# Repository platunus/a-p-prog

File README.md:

# Programmer for 8-bit PIC devices built upon AVR (or Arduino) or WCH CH55x

For [Micro progmeter](https://github.com/jaromir-sukuba/micro_progmeter) project I want to deliver full set of open-source materials, but it would be shame if folks trying to replicate the project would have to buy another programmer to flash the PIC MCU, so I decided to do a little bit of brain stretching and implement PIC16F1xxx programmer with... Arduino. I really can't say I love this platform, but it is low cost and available.
Together with SDCC compiler this serves as completely open-source basis for many 8-bit PIC devices.

The current project status: Programmer working, sources need cleanup, perhaps rework of its structure (it grew out of its simple structure).
# List of supported devices is at the end of this page.

## Hardware
There are two options fo hardware for this project:

### Hardware option 1 - Arduino hardware
Take any Arduino with ATmega328P or ATmega32u4, like Uno, pro micro or most of cheap chinese knock-off boards. Considering the target has its own power supply, connect GND, MCLR, PGC and PGD lines to respective pins on arduino as follows:

| Arduino pin | AVR pin | Target PIC pin | Comment                                                                     |
|-------------|---------|----------------|-----------------------------------------------------------------------------|
| GND         | GND     | GND            | common ground                                                               |
| 5V          | VDD     | VDD            | optional*- power supply for PIC MCU, you may power target from other source |
| A3          | PC3     | MCLR           | reset line of PIC MCU                                                       |
| A1          | PC1     | PGD            | programming data line                                                       |
| A0          | PC0     | PGC            | programming clock line                                                      |

* If you are powering target PIC from other power source (in circuit programming), series resistors (something like 470-1000 Ohms) in MCLR, PGC and PGD lines are good idea, it will somehow decrease currents flowing through IO pins due to power supplies differences between arduino and target board. In this configuration, even targets running at 3,3V are possible to program, though it is dirty practice.

Power it up, no smoke should be released. Run arduino IDE, open programmer firmware from here (/fw/pp.ino), complie and upload to arduino board - now you have PIC programmer ready to go. Go to software below.

The programmer is proven to work with some generic Uno board from china, as well as chinese arduino-nano clone

The [Pro Micro ICSP shield](https://github.com/hanyazou/Pro-Micro-ICSP-shield) is a tiny "shield" for Arduino Pro Micro which featured ATmega32u4.
This tiny board simply connect ATMEGA 32u4's A0, A1 and A3 to PIC's MCLR, PGD and PGC, but acts as a PIC programmer.

### Hardware option 2 - dedicated board
I designed this little board, see at /hw directory

Considering the target has its own power supply, connect GND, MCLR, PGC and PGD lines to respective pins on PIC programmer (notice the pinout similar to PICkit programmers). Vdd line is not currently used ad it is not needed for operation of programmer, but future revisions of firmware may take advantage of this pin and detect target VDD.
The hardware works with both FT232RL and CY7C65213 in place of USB/serial converter. Both were proven to work, with no other hardware difference.

Use [another arduino](https://www.arduino.cc/en/Tutorial/ArduinoISP) (or proper ISP programmer) to load Arduino UNO bootloader to PIC programmer board (performed only once), turning it into regular arduino compatible board.

Ensure JP2 is closed, then you can load new firmware into PIC programmer using regular Arduino IDE. Open jumper JP2. Now you have your programmer ready to go, move on to software.
The firmware should be able to compile outside Arduino IDE as it doesn't contain any Arduino-specific stuff, though I haven't tried that.

### Hardware option 3 - WCH CH552/CH554
Take WCH CH552/CH554 with USB device PHY. Considering the target has its own power supply, connect GND, MCLR, PGC and PGD lines to respective pins on CH55x as follows:

| CH55x pin | Target PIC pin | Comment                                                                     |
|-----------|----------------|-----------------------------------------------------------------------------|
| GND       | GND            | common ground                                                               |
| VDD (5V)  | VDD            | optional*- power supply for PIC MCU, you may power target from other source |
| P1.4      | N/C            | optional- indicator: connected LED with 1k ohm resistor                     |
| P1.5      | MCLR           | reset line of PIC MCU                                                       |
| P1.6      | PGD            | programming data line                                                       |
| P1.7      | PGC            | programming clock line                                                      |

* If you are powering target PIC from other power source (in circuit programming), series resistors (something like 470-1000 Ohms) in MCLR, PGC and PGD lines are good idea, it will somehow decrease currents flowing through IO pins due to power supplies differences between arduino and target board. In this configuration, even targets running at 3,3V are possible to program, though it is dirty practice.

Run arduino IDE, install [CH55xDuino](https://github.com/DeqingSun/ch55xduino), open programmer firmware from here (/fw/pp.ino), select CH552 board, complie and upload to CH55x - now you have PIC programmer ready to go. Go to software below.

## Software

When running under Linux, download source from this repository and run

`gcc -Wall pp3.c -o pp3`

This should build executable pp3. When working under windows, you can download compiled binary from this repository. Alternatively, you can build it from source - install minGW and run

`gcc -Wall pp3.c -o pp3`

ie. the same procedure as on Linux. This should result in silent build with pp3.exe executable created.

Running the executable with no parameters should only bring banner "pp programmer". Though running with basic set of parameters

`./pp3 -c /dev/ttyACM0 -t 16f1829 file.hex`

under Linux, where -c parameter denotes port to be accessed, -t parameter defines PIC to be programmed and last parameter is hex file to be downloaded; or

`pp3.exe -c COM30 -t 16f1829 file.hex`

under Windows should program the target PIC; with expected result:

	$ ./pp3 -c /dev/ttyACM0 -t 16f1829 file.hex
    Opening serial port
    Device ID 0x27E4
    Programming FLASH (16384 B in 256 pages)
    Programming config
    Verifying FLASH (16384 B in 256 pages)
    Verifying config
    Releasing MCLR

## Notes on software

If you are running the hardware on generic arduino board or you forget to open jumper JP2 after loading firmware on dedicated hardware, you may need to insert waiting time after opening serial port and before communication - to ensure Arduino bootloader times out after opening serial port and takes control to programmer firmware. It should look like this

`pp3.exe -c COM30 -s 1700 -t 16f1829 file.bin`

where number after -s switch defines the number of miliseconds to wait after opening the serial port.

You may omit the actual programming using -p switch or verification using -n switch, when using both the programmer only checks target device signature and exits.

`$ ./pp3 -c /dev/ttyACM0 -p -n -t 16f1829 file.bin`

    Opening serial port
    Device ID 0x27E4
    Releasing MCLR

you can add some debug output info using -v parameter, ranging from -v 1 to -v 4. It may be suitable for debugging, -v 4 prints out all byte transaction on serial port, so be prepared for huge output.
There is database file pp3_devices.dat which hold information of supported PIC types. For now, the filename is fixed in code can't be changed and file has to be in the same directory as pp executable..

## Supported devices

Obviously, there is more supported than verified (tested) devices. I tried to test at least one device from specific family. The members from one family are usually very very similar, giving me enough confidence to mark them as supproted. Of course, typos can happen, but those are easy to correct.

**DEVICE**|**TESTED**
:-----:|:-----:
PIC12F1501|YES
PIC12F1571| 
PIC12F1572|YES
PIC12F1612|YES
PIC12F1822|YES
PIC12F1840|YES
PIC12LF1501|YES
PIC12LF1552|YES
PIC12LF1571| 
PIC12LF1572| 
PIC12LF1612| 
PIC12LF1822| 
PIC12LF1840|YES
PIC16F1454| 
PIC16F1455|YES
PIC16F1459| 
PIC16F1503|YES
PIC16F1507|YES
PIC16F1508| 
PIC16F1509|YES
PIC16F1512| 
PIC16F1513| 
PIC16F1516|YES
PIC16F1517| 
PIC16F1518| 
PIC16F1519| 
PIC16F1528| 
PIC16F1529| 
PIC16F15313| 
PIC16F15323| 
PIC16F15324| 
PIC16F15325| 
PIC16F15344| 
PIC16F15345| 
PIC16F15354| 
PIC16F15355|YES
PIC16F15356| 
PIC16F15375| 
PIC16F15376| 
PIC16F15385| 
PIC16F15386| 
PIC16F1574| 
PIC16F1575|YES
PIC16F1578| 
PIC16F1579| 
PIC16F1613|YES
PIC16F1614| 
PIC16F1615|YES
PIC16F1618| 
PIC16F1619|YES
PIC16F1703|YES
PIC16F1704| 
PIC16F1705| 
PIC16F1707| 
PIC16F1708| 
PIC16F1709| 
PIC16F1713| 
PIC16F1716| 
PIC16F1717| 
PIC16F1718|YES
PIC16F1719| 
PIC16F1764| 
PIC16F1765|YES
PIC16F1768| 
PIC16F1769| 
PIC16F1782| 
PIC16F1783|YES
PIC16F1784| 
PIC16F1786| 
PIC16F1787| 
PIC16F1788|YES
PIC16F1789| 
PIC16F1823|YES 
PIC16F1824| 
PIC16F1825|YES 
PIC16F1826| 
PIC16F1827| 
PIC16F1828| 
PIC16F1829|YES
PIC16F18313| 
PIC16F18323| 
PIC16F18324| 
PIC16F18325| 
PIC16F18326| 
PIC16F18344| 
PIC16F18345| 
PIC16F18346|YES
PIC16F18424| 
PIC16F18425| 
PIC16F18426| 
PIC16F18444| 
PIC16F18445| 
PIC16F18446| 
PIC16F18455| 
PIC16F18456| 
PIC16F1847| 
PIC16F18854| 
PIC16F18855|YES
PIC16F18856| 
PIC16F18857| 
PIC16F18875|YES
PIC16F18876| 
PIC16F18877| 
PIC16F19155| 
PIC16F19156|YES
PIC16F19175| 
PIC16F19176|YES
PIC16F19185| 
PIC16F19186| 
PIC16F19195| 
PIC16F19196| 
PIC16F19197| 
PIC16F1933|YES
PIC16F1934| 
PIC16F1936| 
PIC16F1937| 
PIC16F1938| 
PIC16F1939| 
PIC16F1946| 
PIC16F1947| 
PIC16LF1454| 
PIC16LF1455|YES
PIC16LF1459| 
PIC16LF1503|YES
PIC16LF1507| 
PIC16LF1508|YES
PIC16LF1509| 
PIC16LF1512| 
PIC16LF1513| 
PIC16LF1516| 
PIC16LF1517| 
PIC16LF1518| 
PIC16LF1519| 
PIC16LF1528| 
PIC16LF1529| 
PIC16LF15313| 
PIC16LF15323| 
PIC16LF15324| 
PIC16LF15325| 
PIC16LF15344| 
PIC16LF15345| 
PIC16LF15354| 
PIC16LF15355| 
PIC16LF15356| 
PIC16LF15375| 
PIC16LF15376| 
PIC16LF15385| 
PIC16LF15386| 
PIC16LF1574| 
PIC16LF1575| 
PIC16LF1578| 
PIC16LF1579| 
PIC16LF1613| 
PIC16LF1614| 
PIC16LF1615| 
PIC16LF1618| 
PIC16LF1619|
PIC16LF1703| 
PIC16LF1704|YES
PIC16LF1705| 
PIC16LF1707| 
PIC16LF1708| 
PIC16LF1709| 
PIC16LF1713|YES
PIC16LF1716| 
PIC16LF1717| 
PIC16LF1718| 
PIC16LF1719| 
PIC16LF1764| 
PIC16LF1765| 
PIC16LF1768| 
PIC16LF1769| 
PIC16LF1782| 
PIC16LF1783| 
PIC16LF1784| 
PIC16LF1786| 
PIC16LF1787| 
PIC16LF1788| 
PIC16LF1789| 
PIC16LF1824| 
PIC16LF1825| 
PIC16LF1826| 
PIC16LF1827| 
PIC16LF1828| 
PIC16LF1829|YES
PIC16LF18313| 
PIC16LF18323| 
PIC16LF18324| 
PIC16LF18325| 
PIC16LF18326| 
PIC16LF18344| 
PIC16LF18345| 
PIC16LF18346| 
PIC16LF18424| 
PIC16LF18425| 
PIC16LF18444| 
PIC16LF18445| 
PIC16LF18455| 
PIC16LF18456| 
PIC16LF1847| 
PIC16LF18854| 
PIC16LF18855| 
PIC16LF18856| 
PIC16LF18857| 
PIC16LF18875| 
PIC16LF18876| 
PIC16LF18877| 
PIC16LF1902| 
PIC16LF1903|YES
PIC16LF1904| 
PIC16LF1906| 
PIC16LF1907| 
PIC16LF19155| 
PIC16LF19156| 
PIC16LF19175| 
PIC16LF19176| 
PIC16LF19185| 
PIC16LF19186| 
PIC16LF19195| 
PIC16LF19196| 
PIC16LF19197| 
PIC16LF1933| 
PIC16LF1934| 
PIC16LF1936| 
PIC16LF1937| 
PIC16LF1938| 
PIC16LF1939| 
PIC16LF1946| 
PIC16LF1947| 
PIC18F23K22| 
PIC18F24J10|YES
PIC18F24J11| 
PIC18F24J50|YES
PIC18F24K22|YES
PIC18F24K40| 
PIC18F24K42| 
PIC18F24K50| 
PIC18F25J10| 
PIC18F25J11| 
PIC18F25J50| 
PIC18F25K22| 
PIC18F25K40| 
PIC18F25K42| 
PIC18F25K50|YES
PIC18F25K80|YES
PIC18F25Q10|YES
PIC18F26J11|YES
PIC18F26J13| 
PIC18F26J50|YES
PIC18F26J53| 
PIC18F26K22|YES
PIC18F26K40| 
PIC18F26K42| 
PIC18F26K50| 
PIC18F26K80| 
PIC18F26Q10| 
PIC18F27J13| 
PIC18F27J53|YES
PIC18F27K40| 
PIC18F27K42| 
PIC18F27Q10| 
PIC18F43K22| 
PIC18F44J10| 
PIC18F44J11| 
PIC18F44J50| 
PIC18F44K22| 
PIC18F45J10|YES
PIC18F45J11| 
PIC18F45J50| 
PIC18F45K22| 
PIC18F45K40| 
PIC18F45K42| 
PIC18F45K50| 
PIC18F45K80| 
PIC18F45Q10| 
PIC18F46J11| 
PIC18F46J13| 
PIC18F46J50| 
PIC18F46J53| 
PIC18F46K22| 
PIC18F46K40| 
PIC18F46K42| 
PIC18F46K50| 
PIC18F46K80| 
PIC18F46Q10| 
PIC18F47J13| 
PIC18F47J53| 
PIC18F47K40|YES
PIC18F47K42| 
PIC18F47Q10| 
PIC18F47Q43|YES
PIC18F47Q83|YES
PIC18F47Q84|YES
PIC18F55K42| 
PIC18F56K42| 
PIC18F57K42|YES
PIC18F63J11| 
PIC18F63J90| 
PIC18F64J11| 
PIC18F64J90| 
PIC18F65J10| 
PIC18F65J11| 
PIC18F65J15| 
PIC18F65J50| 
PIC18F65J90| 
PIC18F65J94| 
PIC18F65K22| 
PIC18F65K40| 
PIC18F65K80| 
PIC18F65K90| 
PIC18F66J10| 
PIC18F66J11| 
PIC18F66J15|YES
PIC18F66J16| 
PIC18F66J50| 
PIC18F66J55| 
PIC18F66J60| 
PIC18F66J65| 
PIC18F66J90| 
PIC18F66J93| 
PIC18F66J94| 
PIC18F66J99| 
PIC18F66K22| 
PIC18F66K40| 
PIC18F66K80| 
PIC18F66K90| 
PIC18F67J10| 
PIC18F67J11| 
PIC18F67J50|YES
PIC18F67J60| 
PIC18F67J90| 
PIC18F67J93| 
PIC18F67J94| 
PIC18F67K22|YES
PIC18F67K40| 
PIC18F67K90| 
PIC18F83J11| 
PIC18F83J90| 
PIC18F84J11| 
PIC18F84J90| 
PIC18F85J10| 
PIC18F85J11| 
PIC18F85J15| 
PIC18F85J50| 
PIC18F85J90| 
PIC18F85J94| 
PIC18F85K22| 
PIC18F85K90| 
PIC18F86J10| 
PIC18F86J11| 
PIC18F86J15| 
PIC18F86J16| 
PIC18F86J50| 
PIC18F86J55| 
PIC18F86J60| 
PIC18F86J65| 
PIC18F86J72| 
PIC18F86J90| 
PIC18F86J93| 
PIC18F86J94| 
PIC18F86J99| 
PIC18F86K22| 
PIC18F86K90| 
PIC18F87J10| 
PIC18F87J11| 
PIC18F87J50| 
PIC18F87J60| 
PIC18F87J72| 
PIC18F87J90| 
PIC18F87J93| 
PIC18F87J94| 
PIC18F87K22| 
PIC18F87K90| 
PIC18F95J94| 
PIC18F96J60| 
PIC18F96J65| 
PIC18F96J94| 
PIC18F96J99| 
PIC18F97J60| 
PIC18F97J94| 
PIC18LF23K22| 
PIC18LF24J10| 
PIC18LF24J11| 
PIC18LF24J50| 
PIC18LF24K22| 
PIC18LF24K40| 
PIC18LF24K42| 
PIC18LF24K50|YES
PIC18LF25J10| 
PIC18LF25J11| 
PIC18LF25J50| 
PIC18LF25K22|YES
PIC18LF25K40| 
PIC18LF25K42| 
PIC18LF25K50|YES
PIC18LF25K80| 
PIC18LF26J11| 
PIC18LF26J13| 
PIC18LF26J50| 
PIC18LF26J53| 
PIC18LF26K22| 
PIC18LF26K40| 
PIC18LF26K42| 
PIC18LF26K50| 
PIC18LF26K80| 
PIC18LF27J13| 
PIC18LF27J53| 
PIC18LF27K40| 
PIC18LF27K42| 
PIC18LF43K22| 
PIC18LF44J10| 
PIC18LF44J11| 
PIC18LF44J50| 
PIC18LF44K22| 
PIC18LF45J10| 
PIC18LF45J11| 
PIC18LF45J50| 
PIC18LF45K22| 
PIC18LF45K40| 
PIC18LF45K42| 
PIC18LF45K50| 
PIC18LF45K80| 
PIC18LF46J11| 
PIC18LF46J13| 
PIC18LF46J50| 
PIC18LF46J53| 
PIC18LF46K22| 
PIC18LF46K40| 
PIC18LF46K42| 
PIC18LF46K50| 
PIC18LF46K80| 
PIC18LF47J13| 
PIC18LF47J53| 
PIC18LF47K40| 
PIC18LF47K42| 
PIC18LF55K42| 
PIC18LF56K42| 
PIC18LF57K42| 
PIC18LF65K40| 
PIC18LF65K80| 
PIC18LF66K40| 
PIC18LF66K80| 
PIC18LF67K40| 

The whole project is licensed under MIT license, see LICENSE.md file.
Some more details to be found here https://hackaday.io/project/8559-pic16f1xxx-arduino-based-programmer

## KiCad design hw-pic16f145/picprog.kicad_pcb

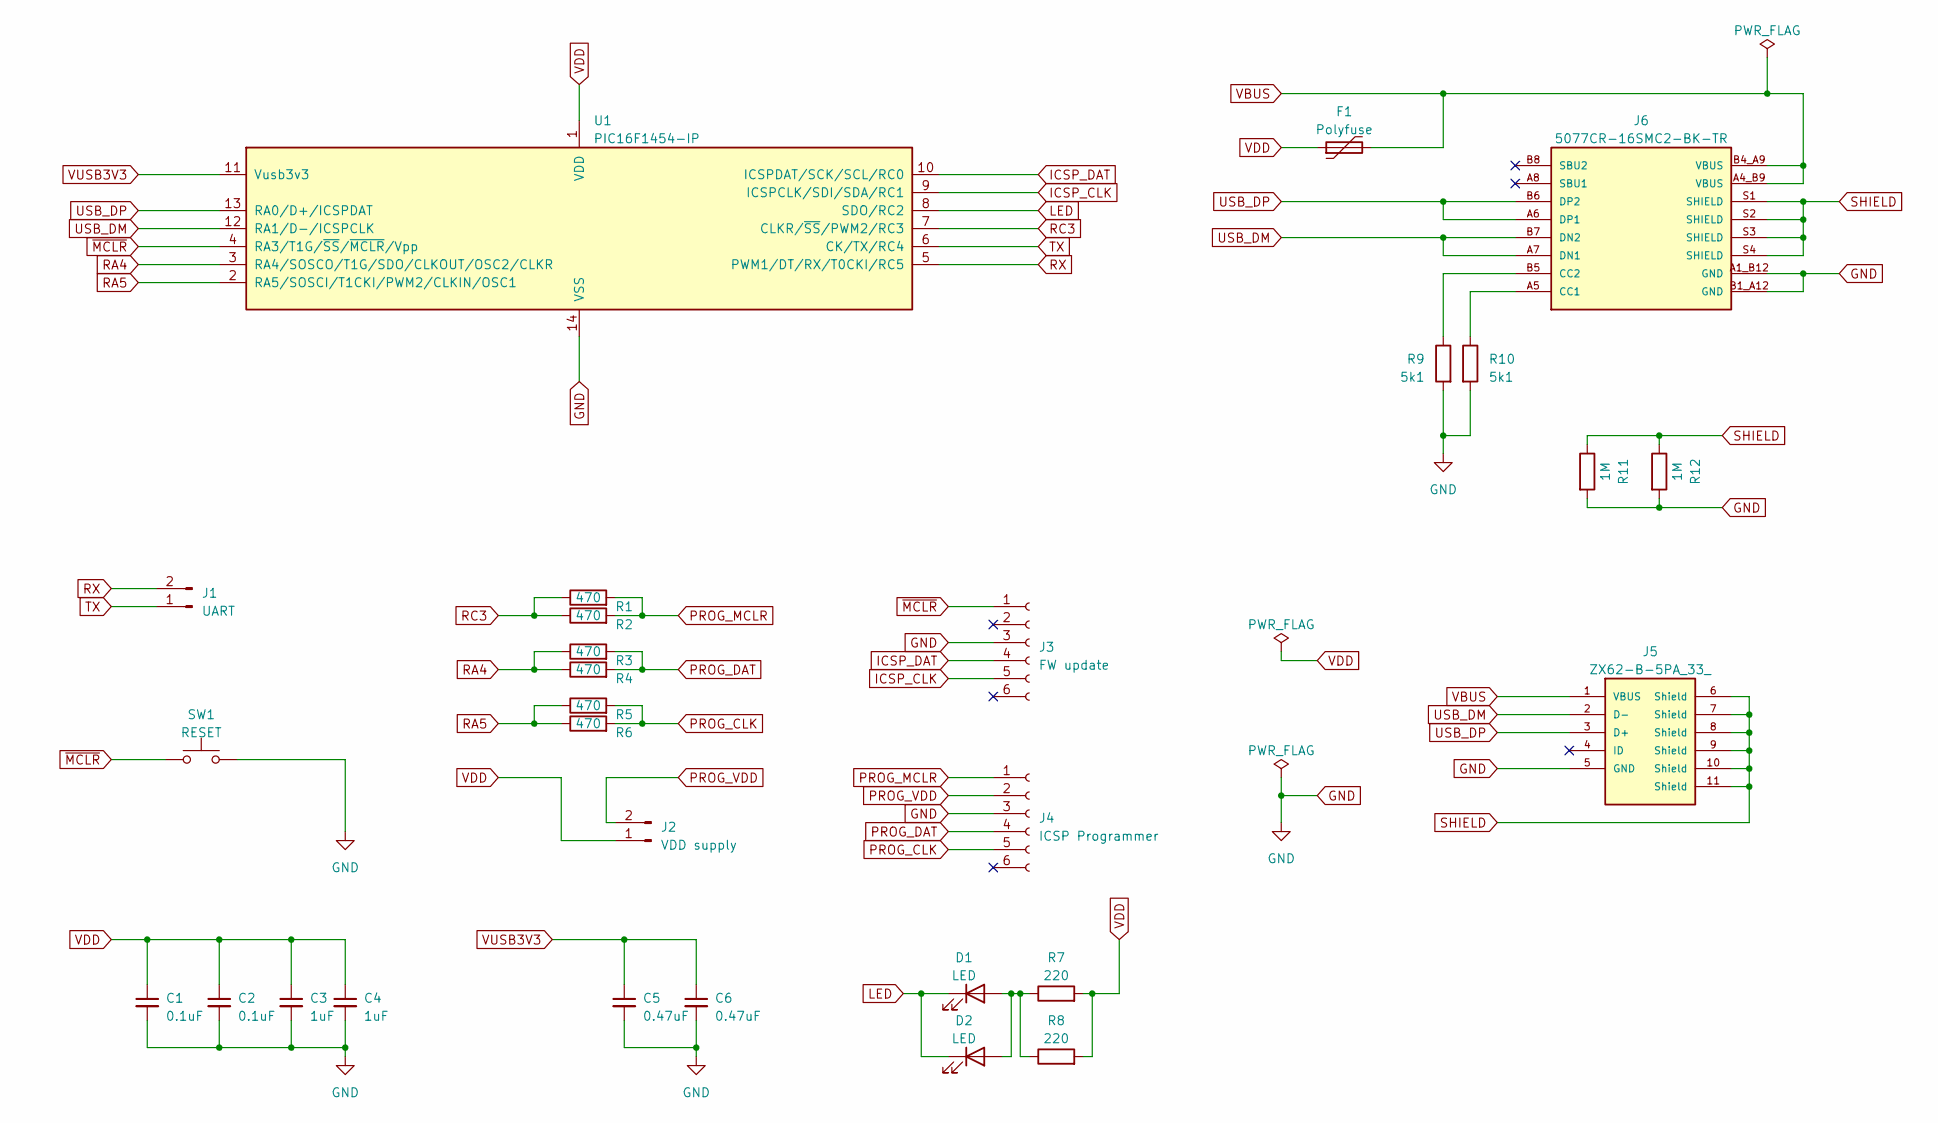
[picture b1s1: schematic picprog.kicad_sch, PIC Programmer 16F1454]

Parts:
C1: 0.1uF; C_0603_1608Metric_Pad1.08x0.95mm_HandSolder
C2: 0.1uF; C_Disc_D4.3mm_W1.9mm_P5.00mm
C3: 1uF; C_0603_1608Metric_Pad1.08x0.95mm_HandSolder
C4: 1uF; C_Disc_D4.3mm_W1.9mm_P5.00mm
C5: 0.47uF; C_0603_1608Metric_Pad1.08x0.95mm_HandSolder
C6: 0.47uF; C_Disc_D4.3mm_W1.9mm_P5.00mm
D1: LED; LED_0805_2012Metric_Pad1.15x1.40mm_HandSolder
D2: LED; LED_D3.0mm
F1: Polyfuse; C_Disc_D5.0mm_W2.5mm_P5.00mm
J1: UART; PinHeader_1x02_P2.54mm_Horizontal
J2: VDD supply; PinHeader_1x02_P2.54mm_Vertical
J3: FW update; PinHeader_1x06_P2.54mm_Horizontal
J4: ICSP Programmer; PinHeader_1x06_P2.54mm_Horizontal
J5: ZX62-B-5PA_33_; ZX62B5PA33; MOUSER_PART_NUMBER 798-ZX62-B-5PA33
J6: 5077CR-16SMC2-BK-TR; NELTRON_5077CR-16SMC2-BK-TR; PARTREV B
R1, R3, R5: 470; R_Axial_DIN0207_L6.3mm_D2.5mm_P10.16mm_Horizontal
R2, R4, R6: 470; R_0603_1608Metric_Pad0.98x0.95mm_HandSolder
R7: 220; R_Axial_DIN0207_L6.3mm_D2.5mm_P10.16mm_Horizontal
R8: 220; R_0603_1608Metric_Pad0.98x0.95mm_HandSolder
R9, R10: 5k1; R_0603_1608Metric_Pad0.98x0.95mm_HandSolder
R11: 1M; R_0603_1608Metric_Pad0.98x0.95mm_HandSolder
R12: 1M; R_Axial_DIN0207_L6.3mm_D2.5mm_P10.16mm_Horizontal
SW1: RESET; push switch
U1: PIC16F1454-IP; DIP-14_W7.62mm_Socket

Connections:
GND: C1.2, C2.2, C3.2, C4.2, C5.2, C6.2, J3.3, J4.3, J5.5 (GND), J6.A1_B12 (GND), J6.B1_A12 (GND), R9.2, R10.2, R11.2, R12.2, SW1.2, U1.14 (VSS)
ICSP_CLK: J3.5, U1.9 (ICSPCLK/SDI/SDA/RC1)
ICSP_DAT: J3.4, U1.10 (ICSPDAT/SCK/SCL/RC0)
LED: D1.1 (K), D2.1 (K), U1.8 (SDO/RC2)
unnamed: D1.2 (A), D2.2 (A), R7.1, R8.1
unnamed: J6.A5 (CC1), R10.1
unnamed: J6.B5 (CC2), R9.1
PROG_CLK: J4.5, R5.2, R6.2
PROG_DAT: J4.4, R3.2, R4.2
PROG_MCLR: J4.1, R1.2, R2.2
PROG_VDD: J2.2, J4.2
RA4: R3.1, R4.1, U1.3 (RA4/SOSCO/T1G/SDO/CLKOUT/OSC2/CLKR)
RA5: R5.1, R6.1, U1.2 (RA5/SOSCI/T1CKI/PWM2/CLKIN/OSC1)
RC3: R1.1, R2.1, U1.7 (CLKR/~SS/PWM2/RC3)
RX: J1.2, U1.5 (PWM1/DT/RX/T0CKI/RC5); also elsewhere on the board
SHIELD: J5.6 (Shield), J5.7 (Shield), J5.8 (Shield), J5.9 (Shield), J5.10 (Shield), J5.11 (Shield), J6.S1 (SHIELD), J6.S2 (SHIELD), J6.S3 (SHIELD), J6.S4 (SHIELD), R11.1, R12.1
TX: J1.1, U1.6 (CK/TX/RC4); also elsewhere on the board
USB_DM: J5.2 (D-), J6.A7 (DN1), J6.B7 (DN2), U1.12 (RA1/D-/ICSPCLK)
USB_DP: J5.3 (D+), J6.A6 (DP1), J6.B6 (DP2), U1.13 (RA0/D+/ICSPDAT)
VBUS: F1.2, J5.1 (VBUS), J6.A4_B9 (VBUS), J6.B4_A9 (VBUS)
VDD: C1.1, C2.1, C3.1, C4.1, F1.1, J2.1, R7.2, R8.2, U1.1 (VDD)
VUSB3V3: C5.1, C6.1, U1.11 (Vusb3v3)
~MCLR: J3.1, SW1.1, U1.4 (RA3/T1G/~SS/~MCLR/Vpp)

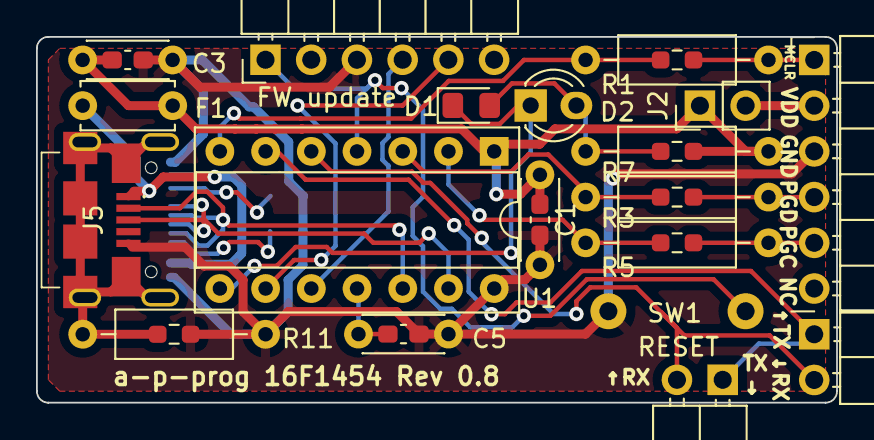
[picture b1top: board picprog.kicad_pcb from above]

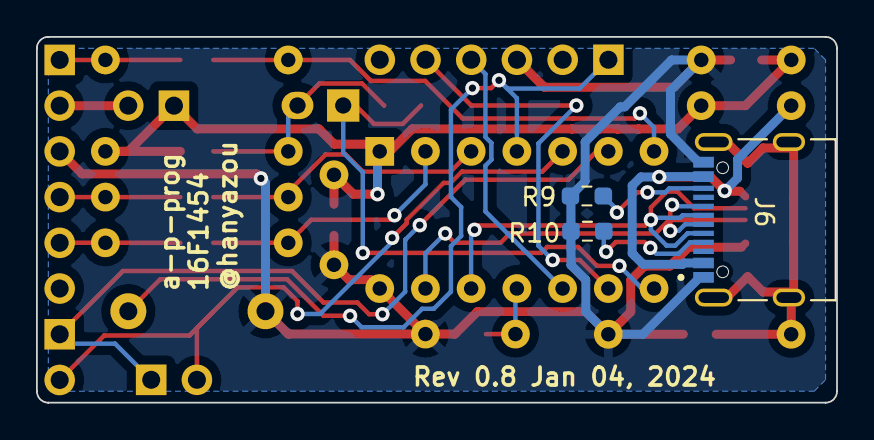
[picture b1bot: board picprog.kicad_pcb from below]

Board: 2 copper layers, 44.4 x 20.3 mm, 30 parts (3 on the bottom side), 23 nets.

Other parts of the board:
J1#2: UART; PinHeader_1x02_P2.54mm_Horizontal

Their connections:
RX: J1#2.2; also elsewhere on the board
TX: J1#2.1; also elsewhere on the board

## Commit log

2023-08-18 Add 18f57q43 to device database
2023-10-09 Add description of pro micro shield
2023-12-09 Re-indent pp.ino
2023-12-10 Ignore config data which are out of address range
2023-12-10 Re-indent pp3.c
2023-12-23 Add info/debug/verbose print wrappers
2023-12-26 fw: Add exec_ops()
2023-12-26 fw: Add debug_print()
2023-12-27 sw: Suppress verbose messages from input file parsers
2023-12-27 sw: Use pp_ops*() for PIC 18F47Qxx
2023-12-28 sw: Add chip_family_t *cf and pp3_p18qxx.c
2023-12-28 fw: Add fw_pp_ops.c
2023-12-28 fw: Add fw_pp_ops.h
2023-12-28 fw: Add OP_READ_ISP_BITS and OP_WRITE_ISP_BITS
2023-12-28 sw: Use read/write_isp_bits()
2023-12-28 example: Add hello-serial, tiny PIC 18F47Q43 project
2023-12-28 sw: Restore non pp_ops routines in pp3.c
2024-01-02 example: hello-serial: Change baud rate to 115200
2024-01-02 fw: Tweak debug output of fw_pp_ops.c
2024-01-02 fw-pic16f145: re-indent (cosmetic changes)
2024-01-02 fw-pic16f145: Fix project to 'a-p-prog-fw-pic'
2024-01-02 fw-pic16f145: Add project (copy of cdc_acm_x2)
2024-01-02 fw-pic16f145: Add submoudle m-stack
2024-01-03 fw-pic16f145: Add a-p-prog FW
2024-01-03 fw-pic16f145: Handle break condition
2024-01-03 fw-pic16f145: Improve UART to USB converter buffering
2024-01-03 fw-pic16f145: Add UART to USB converter function
2024-01-03 fw-pic16f145: Use periodic timer interrupt
2024-01-04 hw-pic16f145: Add picprog PCB rev 0.8
2024-01-06 sw: Add cf->odd_mask and even_mask
2024-01-06 sw: Add pp_ops_isp_send*() and pp_util_revert_bit_order()
2024-01-06 fw: Shift to MSB side if less than 8 bits in OP_READ_ISP_BITS
2024-01-06 fw: Send CMD2 after sending data
2024-01-06 sw: Rename pp3_p18qxx.c to cf_p18f_qxx.c
2024-01-06 sw: Fix length argument of pp_ops_read_isp_bits()
2024-01-06 sw: Add cf->reset_pointer()
2024-01-06 sw: Add legacy mode to use existing chip_family routunes
2024-01-06 sw: Add verify only option
2024-01-07 sw: Add cf->increase_pointer()
2024-01-07 sw: Return non-zero exit status on error
2024-01-07 sw: Tweak output/error messages
2024-01-07 fw-pic16f145: Use PK5Tool for platformTool
2024-01-07 fw-pic16f145: Enable Low-Voltage Programming in configration word 2
2024-01-07 fw-pic16f145: Add copy m-stack/apps/common/hardware.c
2024-01-07 sw: Fix P16F configration memory verification error messages
2024-01-07 sw: Add pp_util_hexdump()
2024-01-07 sw: Add CF_P16F_A chip family support
2024-01-07 Add copyright notices
2024-01-07 sw: Rename COM to com_port_name
2024-01-07 sw: Add comm.c and move communication functions into it
2024-01-07 sw: Add cf->reset_target()
2024-01-07 sw: Add main.c (copy of pp3.c)
2024-01-08 sw: Sweep out legacy portions into splitted pp3.c
2024-01-08 Get rid of #ifdef PP_EXEC_OPS and PP_EXEC_OPS_RW_BITS
2024-01-08 Check protocol version and firmware capabilities
2024-01-08 fw-pic16f145: Enable compiler optimization (-O2)
2024-01-08 sw: Exit if the device id does not match to expected
2024-01-08 fw-pic16f145: Add buffer for pp_ops result bytes
2024-01-08 fw-pic16f145: Optimize/decrease delay
2024-01-08 pp_ops: Optimize/reduce delay of read and write bits
2024-01-08 fw-pic16f145: Enable compiler optimization (-O3)
2024-01-08 sw: Combine parameter setting and page read/write to speed up
2024-01-08 fw: Add PP_CAP_ASYNC_WRITE
2024-01-08 sw: cf_p18f_qxx: Remove waiting for completion in cf_p18f_q_write_page()
2024-01-13 sw: cf_p16f_a: Read configuration words at once
2024-01-14 example: Add small LED blink program
2024-01-14 example: hello-blink: Add PIC16F18857 configuration and .hex
2024-01-14 example: hello-blink: Add PIC16F18313 configuration and .hex
2024-01-14 sw: Fix pp_util_hexdump()
2024-01-14 sw: Add CF_P16F_C chip family support
2024-01-14 sw: Add pp_ops_isp_send_*_msb() helper functions
2024-01-14 sw: Add CF_P16F_D chip family support
2024-01-14 example: hello-blink: Add PIC16F1503 configuration and .hex
2024-01-14 sw: Add cf_p16f_c.c and move cf_p16f_c_*() functions in to it
2024-01-14 sw: Add CF_P16F_B chip family support
2024-01-14 sw: cf_p16f_b: Read more configration words in cf_p16f_b_read_config()
2024-01-14 sw: Move verify configuration debug message into main.c and pp3.c
2024-02-10 sw: Change {read|write}_page() to {read|write}_program()
2024-02-10 fw-pic16f145: Update PID/VID and string descriptors
2024-11-05 feat: add CH55x support
2024-11-05 chore: modify README.md
